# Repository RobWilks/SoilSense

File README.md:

# SoilSense
Measurement of capacitance of soil probe to determine moisture content of soil
Uses an LC oscillator at f from 50-100MHz
Frequency of oscillation is proportional to the inverse root of capacitance

At these frequencies and temperatures 0 < T < 30 degC the dielectric function of water is ~80; small changes in soil moisture content create a large change in capacitance

There are two physical prototypes, mark I & II:

Mark I
Uses a Clapp oscillator and emitter follower with BC547B transistors.  In the tank circuit is a toroidal inductor of 13-16 turns and 3x 22pF capacitors.
Base input and stray capacitance estimated as 7 and 3 respectively.  

Mark II
Uses a Motorola VCO MC1648 a toroidal inductor of 9 turns and 10pF cpacitor in the tank circuit (adds to input capacitance of 6pF)

Marks I & II use the same prescaler and counter circuits to convert the high frequency oscillation to a low frequency square wave, reducing the frequency by 1/2^17 

The low frequency is measured using a 16MHz 5V Promini and the result sent to a gateway using a cheap 433MHz RF transmitter 

Repository contains:

Clapp circuit 181226.log	:	LTSpice simulation of Clapp oscillator and transmission line

ReadNodeDataNew.R	:	R analysis of data from soil probe

Schematic_Soil-Sense-Mark-1_buffered-Clapp-circuit_20181225231505.pdf	:	Schematic of circuit for SoilSenseMark1 from EasyEDA

SketchVxx.cpp	:	Old - hidden

SoilSenseMark1	:	C++ code for ProMini measurement and reporting sequence

SoilSenseMark2	:	C++ code for ProMini measurement and reporting sequence

SoilSenseMark2_board.pdf	:	Vero board design for SoilSenseMark2 from Eagle

SoilSenseMark2_schematic.pdf	:	Schematic of circuit for SoilSenseMark2 from Eagle

freqCounterV4.brd	:	Vero board design for SoilSenseMark2 from Eagle

freqCounterV4.sch	:	Schematic of circuit for SoilSenseMark2 from Eagle

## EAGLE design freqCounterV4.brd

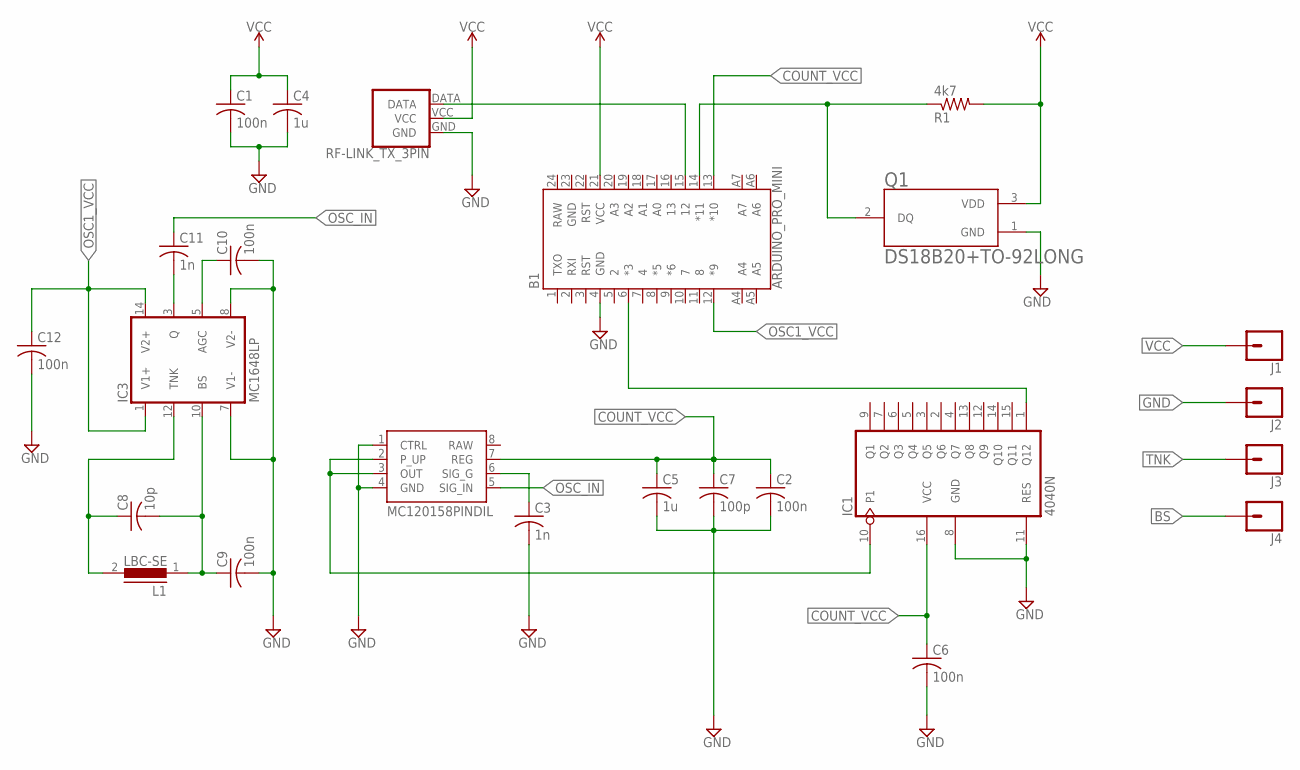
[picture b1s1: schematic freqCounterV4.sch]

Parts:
B1: ARDUINO_PRO_MINI
C1, C2, C9, C10, C12: 100n; C050-025X075
C3: 1n; C050-025X075
C4: 1u; C025-025X050
C5: 1u; C050-025X075
C6: 100n; C075-032X103
C7: 100p; C050-025X075
C8: 10p; C050-025X075
C11: 1n; C075-032X103
IC1: 4040N; DIL16
IC2: MC120158PINDIL; DIL08
IC3: MC1648LP; DIL14
J1, J2, J3, J4: CONN_01; 1X01
L1: LBC-SE
Q1: DS18B20+TO-92LONG; TO-92_0.1"
R1: 4k7; 0204V
U$2: RF-LINK_TX_3PIN

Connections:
BS: C8.2, C9.1, IC3.10 (BS), J4.1, L1.1
COUNT_VCC: B1.13 (*10), C2.1, C5.1, C6.1, C7.1, IC1.16 (VCC), IC2.7 (REG)
GND: B1.4 (GND), B1.23 (GND), C1.2, C2.2, C3.2, C4.2, C5.2, C6.2, C7.2, C9.2, C10.2, C12.2, IC1.8 (GND), IC1.11 (RES), IC2.1 (CTRL), IC2.4 (GND), IC3.7 (V1-), IC3.8 (V2-), J2.1, Q1.1 (GND), U$2.GND
unnamed: IC1.10 (P1), IC2.2 (P_UP), IC2.3 (OUT)
unnamed: C3.1, IC2.6 (SIG_G)
unnamed: B1.6 (*3), IC1.1 (Q12)
unnamed: C11.2, IC3.3 (Q)
unnamed: B1.15 (12), U$2.DATA
unnamed: B1.14 (*11), Q1.2 (DQ), R1.1
unnamed: C10.1, IC3.5 (AGC)
OSC1_VCC: B1.12 (*9), C12.1, IC3.1 (V1+), IC3.14 (V2+)
OSC_IN: C11.1, IC2.5 (SIG_IN)
RAW: B1.24 (RAW), IC2.8 (RAW)
TNK: C8.1, IC3.12 (TNK), J3.1, L1.2
VCC: B1.21 (VCC), C1.1, C4.1, J1.1, Q1.3 (VDD), R1.2, U$2.VCC

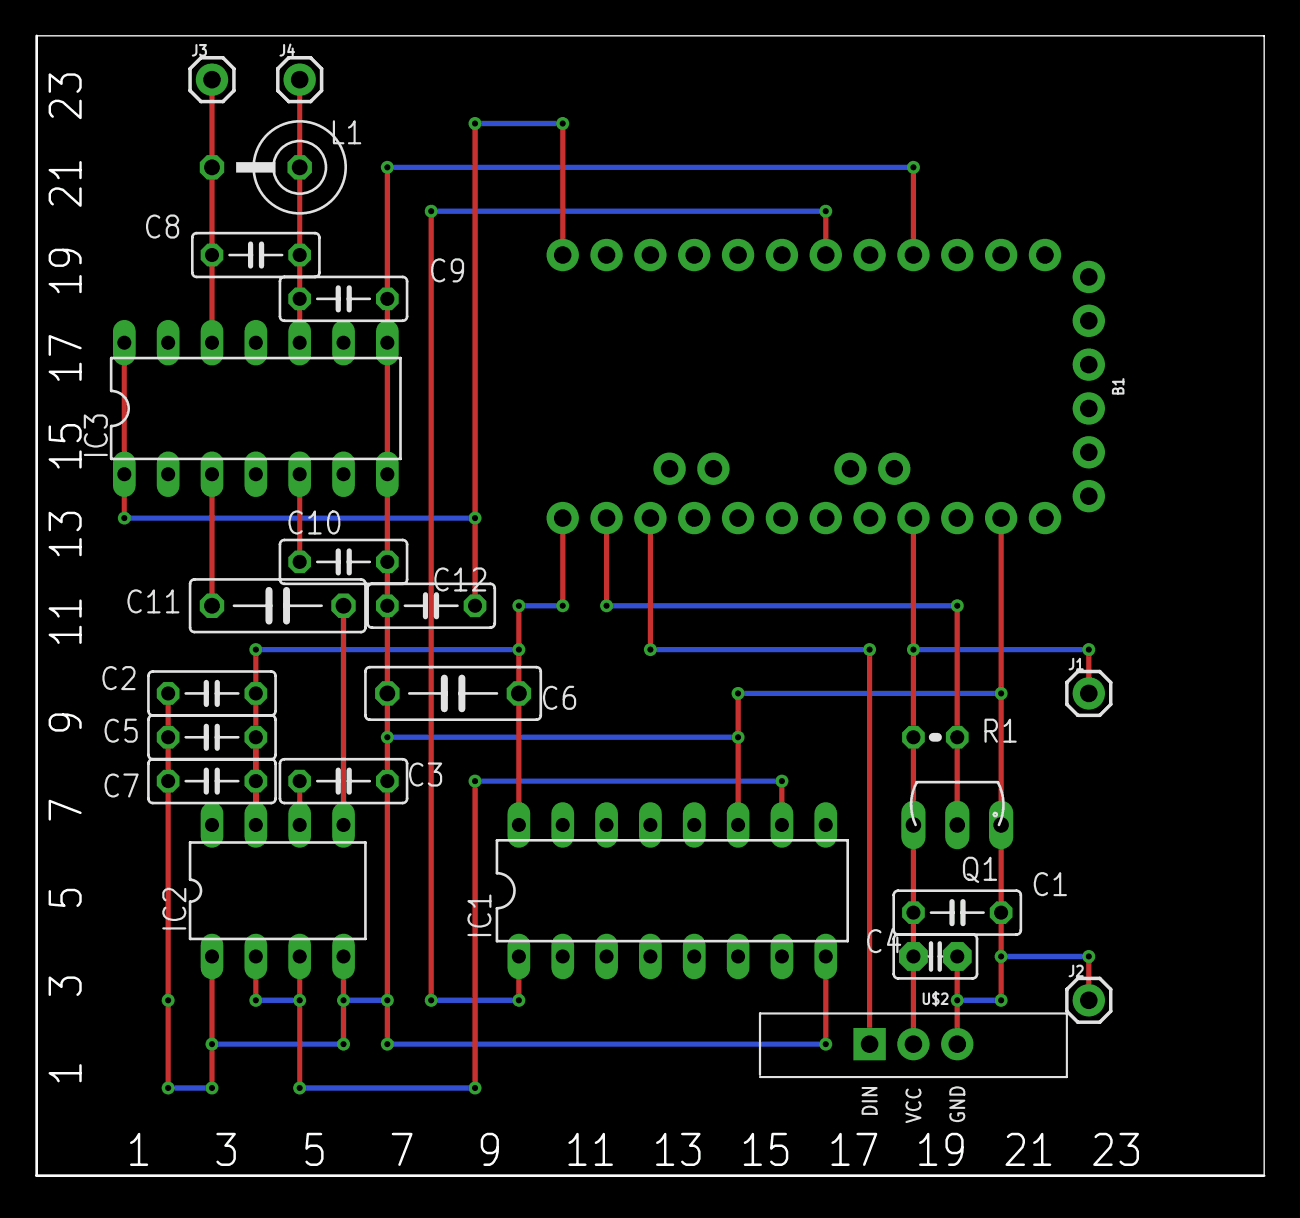
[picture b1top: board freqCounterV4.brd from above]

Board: 2 copper layers, 71.2 x 66.4 mm, 24 parts (0 on the bottom side), 15 nets.

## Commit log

2018-12-18 Add files via upload
    11/12/2018 0759
2018-12-18 Rename SketchV6.cpp to SketchVxx.cpp
2018-12-18 Now for commitment
2018-12-25 Create README.md
    Summary of project and repository
2018-12-25 Create SoilSenseMark1
    Mark1 2x Clapp oscillator: 1) reference oscillator and 2) oscillator with soil probe in LC tank
2018-12-25 Create SoilSenseMark2
2018-12-25 Update SoilSenseMark1
2018-12-25 Add files via upload
    EasyEDA schematic for mark 1 soil sense used for circuit simulation
    Original file: https://easyeda.com/editor#id=1ef8bae271db412c9a281e64cfd3d1a0|20bc0ac2db31423f8fcb9775d9d21192
2018-12-25 Add files via upload
    R script to analyse data from soil sense nodes
2018-12-25 Add files via upload
    Eagle files for soil sensor Mark 2
2019-01-07 Update SoilSenseMark2
2019-01-07 Create temp
2019-01-07 Rename SketchVxx.cpp to SoilSenseMark1.cpp
2019-01-07 Rename SoilSenseMark1 to SoilSenseMark1.cpp
2019-01-07 Rename SoilSenseMark2 to SoilSenseMark2.cpp

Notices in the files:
parts and their libraries:
SparkFun-Boards: Licensing: Creative Commons ShareAlike 4.0 International - https://creativecommons.org/licenses/by-sa/4.0
